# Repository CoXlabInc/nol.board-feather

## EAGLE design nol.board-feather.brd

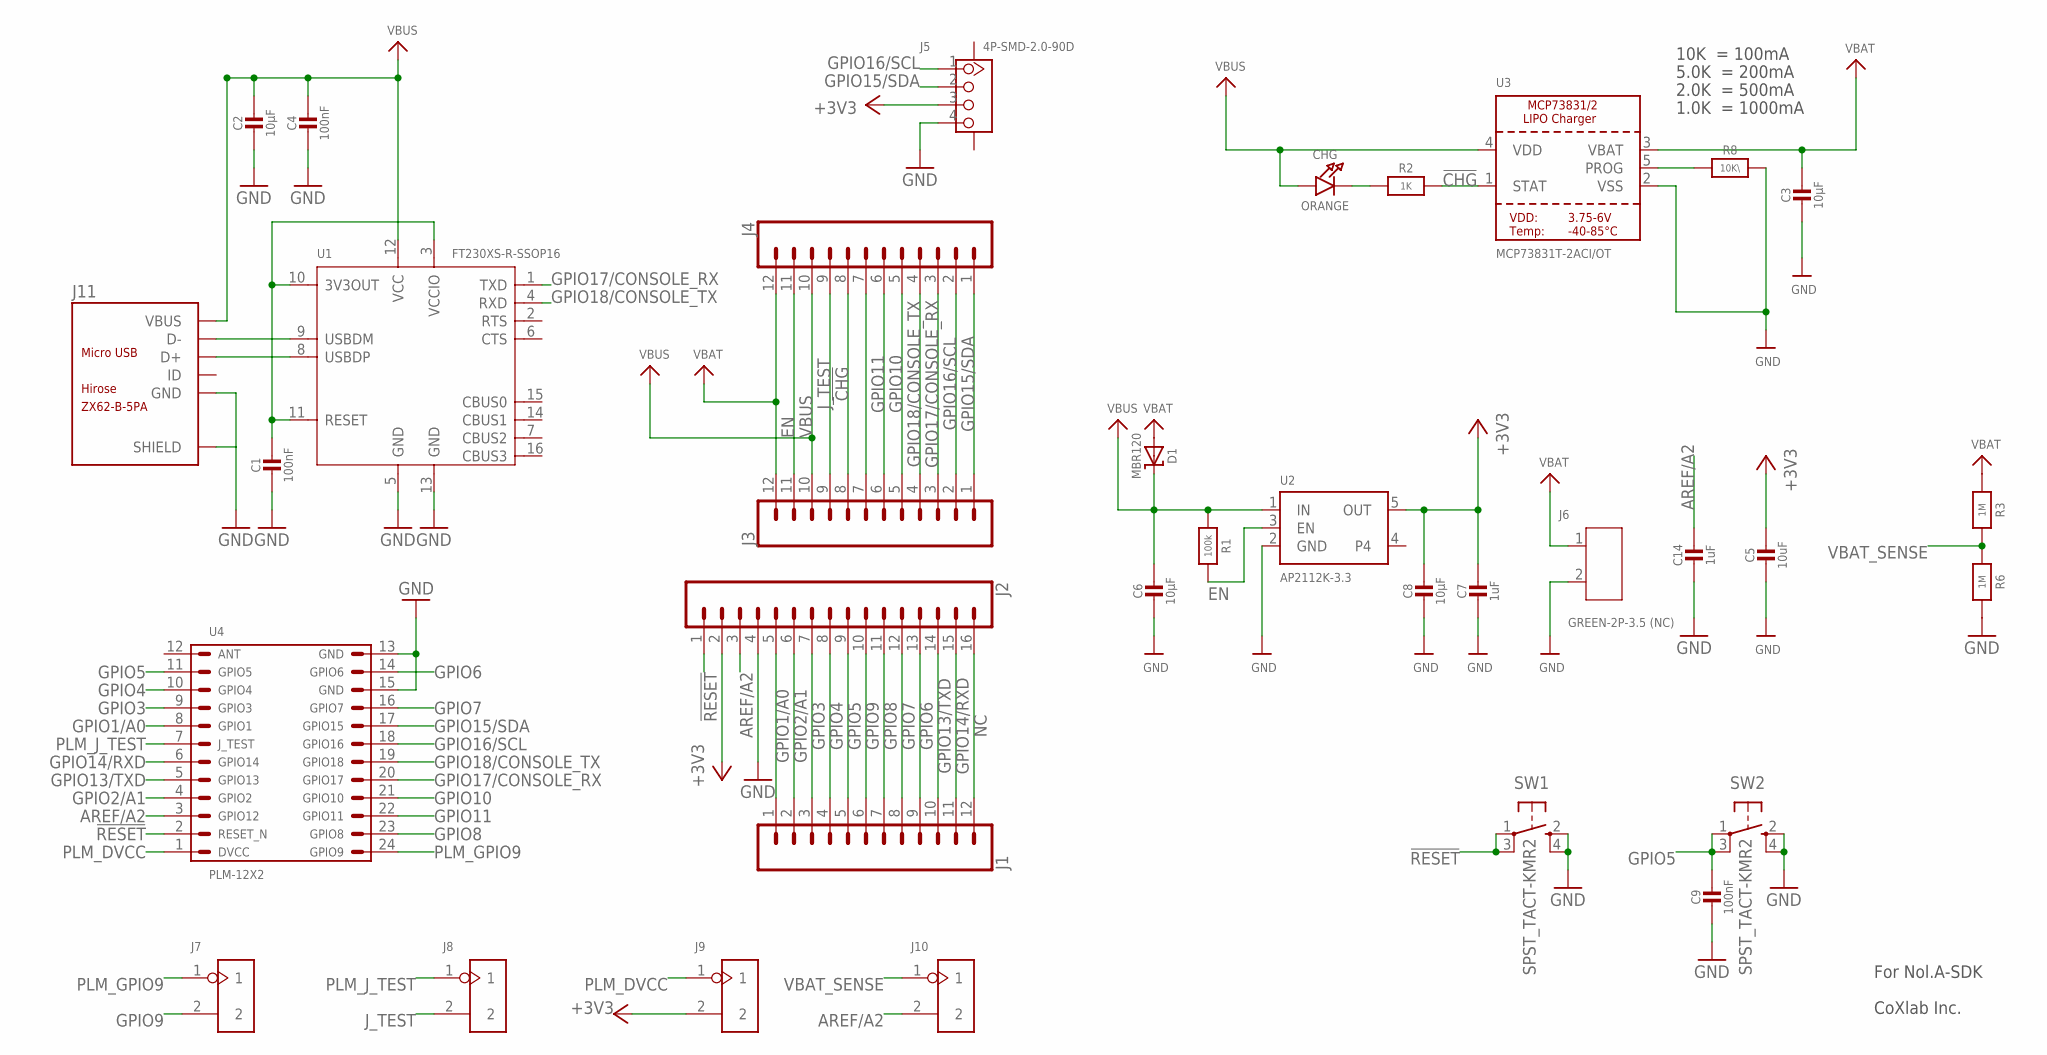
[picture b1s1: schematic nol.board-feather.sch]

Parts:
C1, C4, C9: 100nF; 0805-NO
C2, C3, C6, C8: 10µF; 0805-NO
C5: 10uF; 0805-NO
C7, C14: 1uF; 0603-NO
CHG: ORANGE; CHIPLED_0805_NOOUTLINE
D1: MBR120; SOD-123
J1, J3, J4: CONN_12; 1X12
J2: CONN_16; 1X16
J5: 4P-SMD-2.0-90D; HW4-SMD-2.0-90D
J6: GREEN-2P-3.5 (NC); H2-3.5-7.0X7.0MM
J7, J8, J9, J10: DIP-BLACK-JUMPER; H2-2.54
J11: ZX62-B-5PA; MICRO-USB5+6P-SMD-0.65-AB
R1: 100k; 0603-NO
R2: 1K; 0603-NO
R3, R6: 1M; 0603-NO
R8: 10K\; 0603-NO
SW1, SW2: SPST_TACT-KMR2; KMR2
U1: FT230XS-R-SSOP16; SSOP16-0.635-5X4MM
U2: AP2112K-3.3; SOT23-5
U3: MCP73831T-2ACI/OT; SOT23-5
U4: PLM-12X2
U$1: COXLAB5X5MM; COXLAB_5X5MM
U$7: NOLA10X10MM; NOLA_10X10MM

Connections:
!CHG: J3.8, J4.8, R2.2, U3.1 (STAT)
!RESET: J2.1, SW1.1, SW1.3 (P1), U4.2
+3V3: C5.1, C7.1, C8.1, J2.2, J5.3, J9.2, U2.5 (OUT)
AREF/A2: C14.1, J2.3, J10.2, U4.3
EN: J3.11, J4.11, R1.2, U2.3 (EN)
GND: C1.2, C2.2, C3.2, C4.2, C5.2, C6.2, C7.2, C8.2, C9.2, C14.2, J2.4, J5.4, J6.2, J11.5 (GND), J11.P1 (SHIELD), J11.P2 (SHIELD), J11.P3 (SHIELD), J11.P4 (SHIELD), J11.P5 (SHIELD), J11.P6 (SHIELD), R6.2, R8.2, SW1.2 (S), SW1.4 (S1), SW2.2 (S), SW2.4 (S1), U1.5 (GND), U1.13 (GND), U2.2 (GND), U3.2 (VSS), U4.13, U4.15
GPIO1/A0: J1.1, J2.5, U4.8
GPIO2/A1: J1.2, J2.6, U4.4
GPIO3: J1.3, J2.7, U4.9
GPIO4: J1.4, J2.8, U4.10
GPIO5: C9.1, J1.5, J2.9, SW2.1, SW2.3 (P1), U4.11
GPIO6: J1.9, J2.13, U4.14
GPIO7: J1.8, J2.12, U4.16
GPIO8: J1.7, J2.11, U4.23
GPIO9: J1.6, J2.10, J7.2
GPIO10: J3.5, J4.5, U4.21
GPIO11: J3.6, J4.6, U4.22
GPIO13/TXD: J1.10, J2.14, U4.5
GPIO14/RXD: J1.11, J2.15, U4.6
GPIO15/SDA: J3.1, J4.1, J5.2, U4.17
GPIO16/SCL: J3.2, J4.2, J5.1, U4.18
GPIO17/CONSOLE_RX: J3.3, J4.3, U1.1 (TXD), U4.20
GPIO18/CONSOLE_TX: J3.4, J4.4, U1.4 (RXD), U4.19
J_TEST: J3.9, J4.9, J8.2
unnamed: J11.2 (D-), U1.9 (USBDM)
unnamed: J11.3 (D+), U1.8 (USBDP)
unnamed: C1.1, U1.3 (VCCIO), U1.10 (3V3OUT), U1.11 (RESET)
unnamed: J3.7, J4.7
unnamed: CHG.C, R2.1
unnamed: R8.1, U3.5 (PROG)
NC: J1.12, J2.16
PLM_DVCC: J9.1, U4.1
PLM_GPIO9: J7.1, U4.24
PLM_J_TEST: J8.1, U4.7
VBAT: C3.1, D1.A, J3.12, J4.12, J6.1, R3.1, U3.3 (VBAT)
VBAT_SENSE: J10.1, R3.2, R6.1
VBUS: C2.1, C4.1, C6.1, CHG.A, D1.C, J3.10, J4.10, J11.1 (VBUS), R1.1, U1.12 (VCC), U2.1 (IN), U3.4 (VDD)

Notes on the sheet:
10K = 100mA
5.0K = 200mA
2.0K = 500mA
1.0K = 1000mA

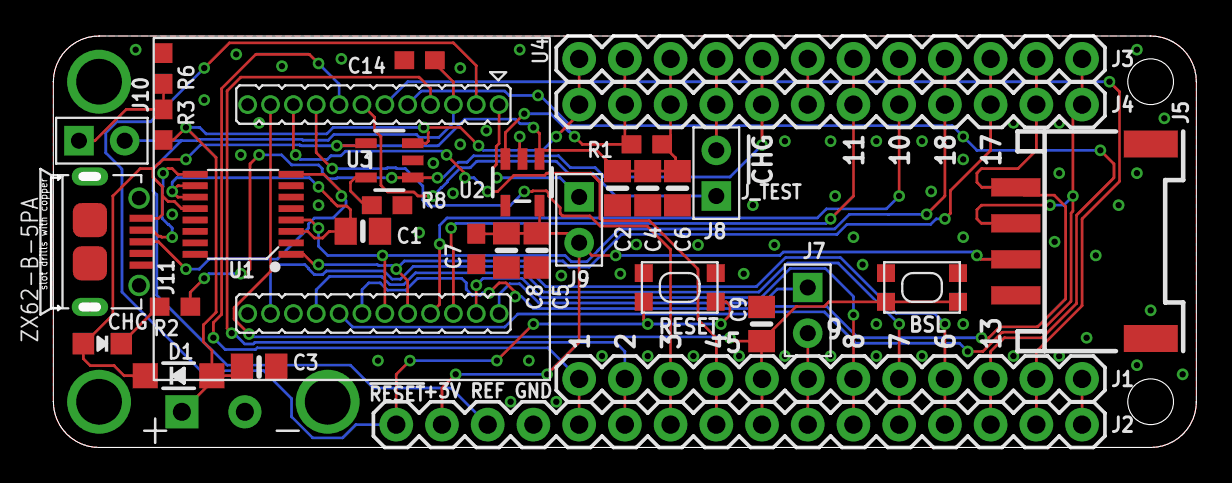
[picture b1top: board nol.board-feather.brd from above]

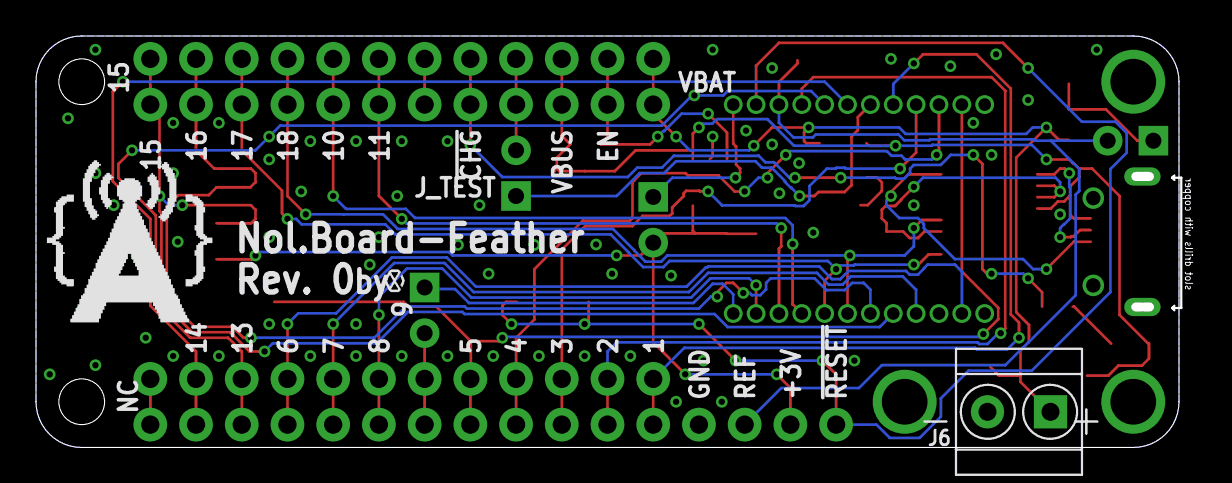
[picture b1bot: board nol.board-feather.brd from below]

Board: 2 copper layers, 64.0 x 22.4 mm, 36 parts (3 on the bottom side), 37 nets.

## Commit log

2019-03-29 DK-1 Added schematic and board artwork.
2019-04-01 DK-1 Added BOM. Finished with order.

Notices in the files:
parts and their libraries:
SparkFun-Connectors: Licensing: Creative Commons ShareAlike 4.0 International - https://creativecommons.org/licenses/by-sa/4.0
microbuilder: This work is placed in the public domain, and may be freely used for commercial and non-commercial work with the following conditions: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
